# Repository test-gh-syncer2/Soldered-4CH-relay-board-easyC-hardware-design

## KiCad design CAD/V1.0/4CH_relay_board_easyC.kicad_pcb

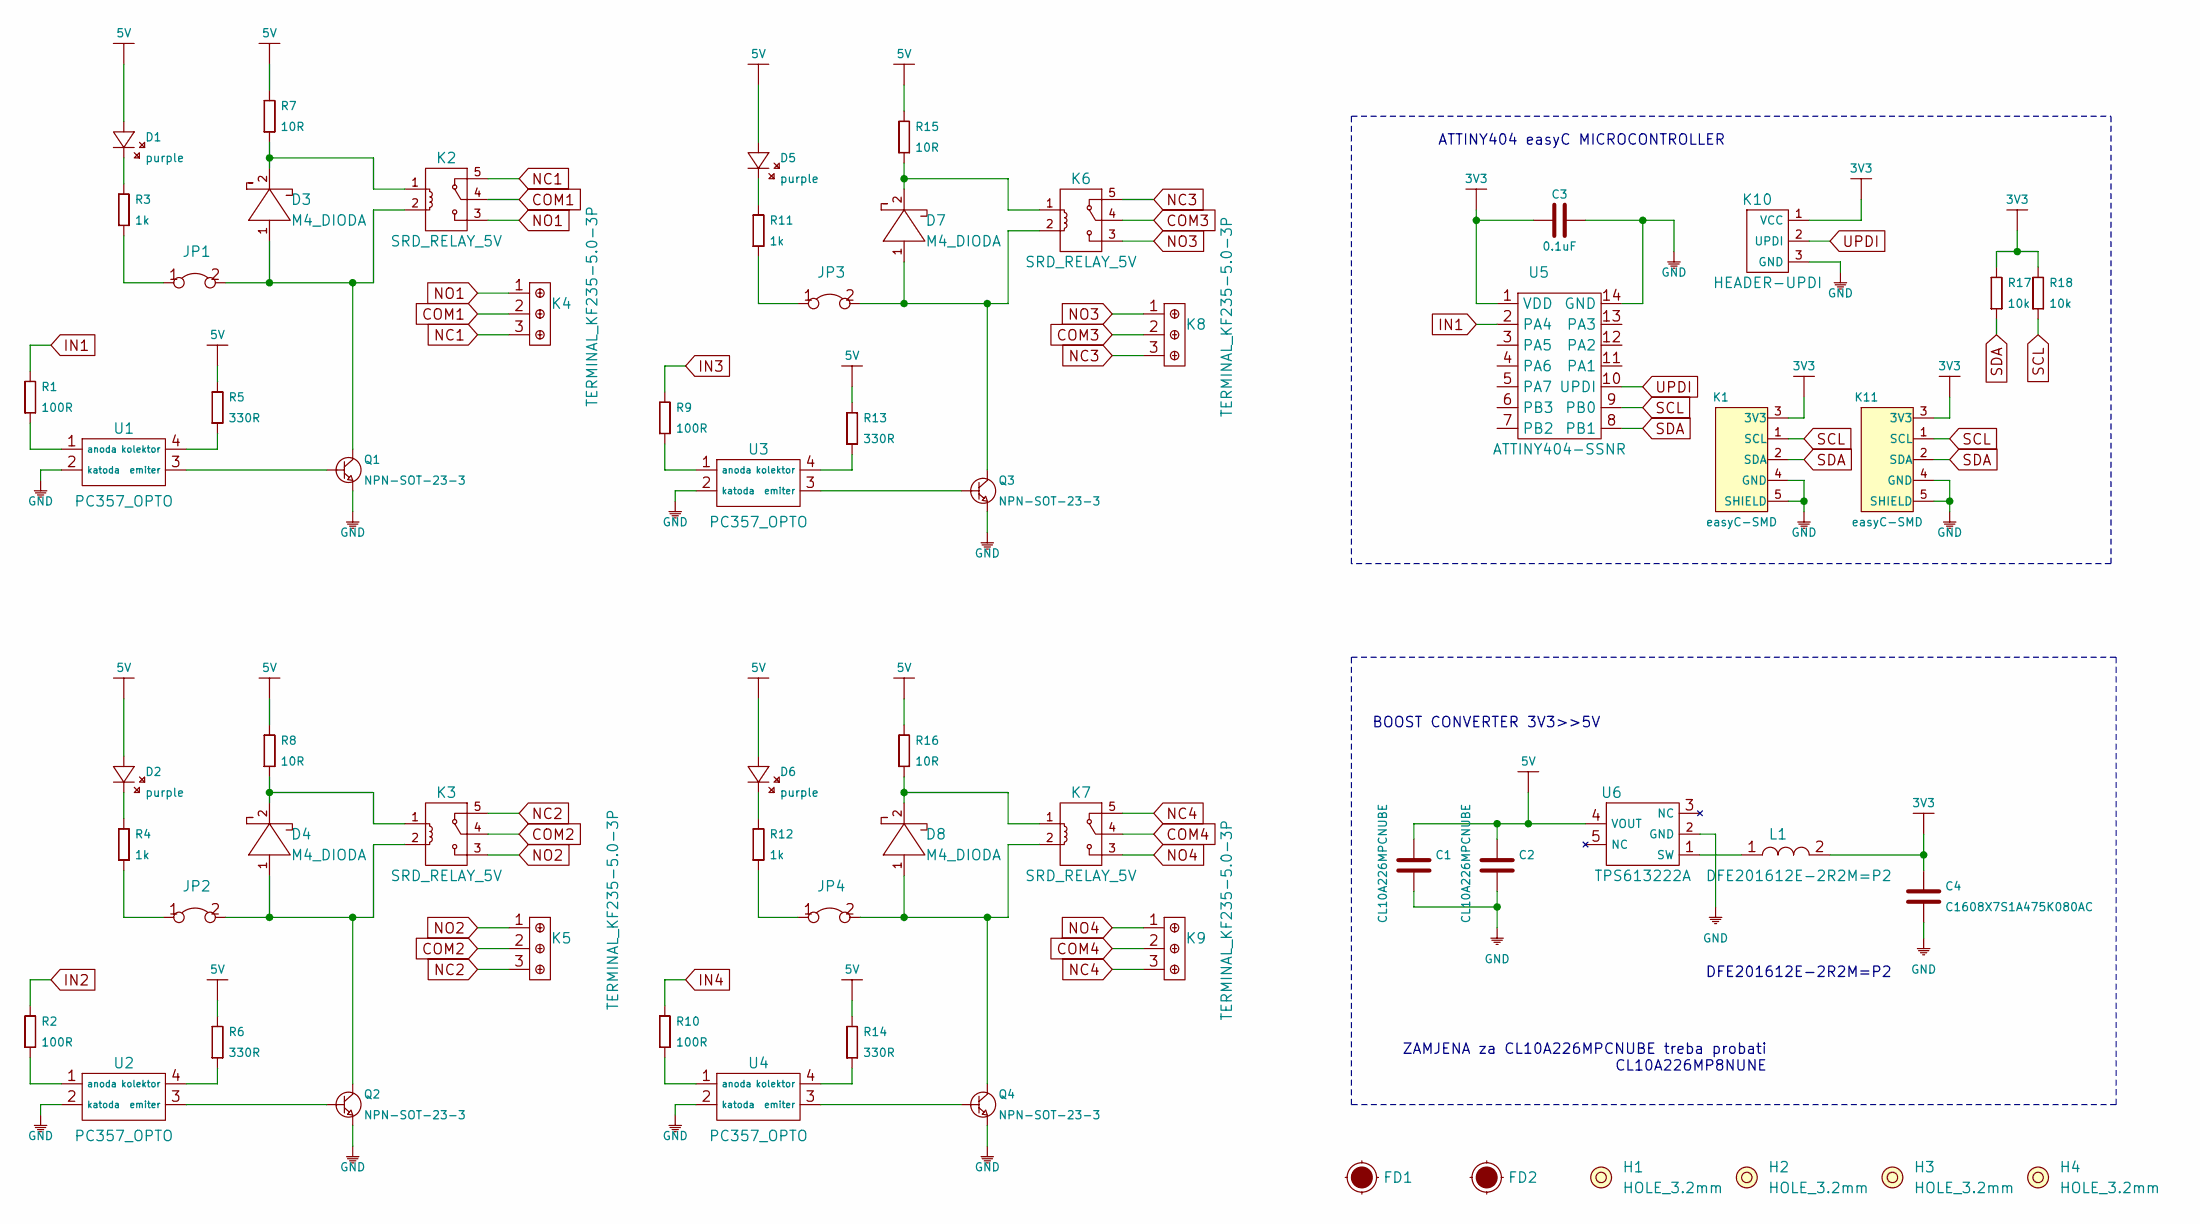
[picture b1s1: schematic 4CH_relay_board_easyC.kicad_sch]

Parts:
C1, C2: CL10A226MPCNUBE; 0603C
C3: 0.1uF; 0603C
C4: C1608X7S1A475K080AC; 0603C
D1, D2, D5, D6: purple; 0402LED
D3, D4, D7, D8: M4_DIODA
FD1, FD2: Fiducial_Stencil; FIDUCIAL_1MM_PASTE
H1, H2, H3, H4: HOLE_3.2mm
JP1, JP2, JP3, JP4: SMD-JUMPER-CONNECTED_TRACE_NOSLODERMASK
K1, K11: easyC-SMD; easyC-connector
K2, K3, K6, K7: SRD_RELAY_5V
K4, K5, K8, K9: TERMINAL_KF235-5.0-3P
K10: HEADER-UPDI
L1: DFE201612E-2R2M=P2; 0806L
Q1, Q2, Q3, Q4: NPN-SOT-23-3; SOT-23-3
R1, R2, R9, R10: 100R; 0603R
R3, R4, R11, R12: 1k; 0402R
R5, R6, R13, R14: 330R; 0603R
R7, R8, R15, R16: 10R; 0603R
R17, R18: 10k; 0603R
U1, U2, U3, U4: PC357_OPTO
U5: ATTINY404-SSNR; SOIC-14
U6: TPS613222A; tps613222a

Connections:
3V3: C3.1, C4.2, K1.3 (3V3), K10.1 (VCC), K11.3 (3V3), L1.2, R17.2, R18.2, U5.1 (VDD)
5V: C1.2, C2.2, D1.1 (A), D2.1 (A), D5.1 (A), D6.1 (A), R5.2, R6.2, R7.2, R8.2, R13.2, R14.2, R15.2, R16.2, U6.4 (VOUT)
COM1: K2.4, K4.2
COM2: K3.4, K5.2
COM3: K6.4, K8.2
COM4: K7.4, K9.2
GND: C1.1, C2.1, C3.2, C4.1, K1.4 (GND), K1.5 (SHIELD), K10.3 (GND), K11.4 (GND), K11.5 (SHIELD), Q1.2 (E), Q2.2 (E), Q3.2 (E), Q4.2 (E), U1.2 (katoda), U2.2 (katoda), U3.2 (katoda), U4.2 (katoda), U5.14 (GND), U6.2 (GND)
IN1: R1.2, U5.2 (PA4)
IN2: R2.2
IN3: R9.2
IN4: R10.2
NC1: K2.5, K4.3
NC2: K3.5, K5.3
NC3: K6.5, K8.3
NC4: K7.5, K9.3
NO1: K2.3, K4.1
NO2: K3.3, K5.1
NO3: K6.3, K8.1
NO4: K7.3, K9.1
unnamed: D1.2 (K), R3.2
unnamed: D2.2 (K), R4.2
unnamed: D3.1 (A), JP1.2, K2.2, Q1.3 (C)
unnamed: D3.2 (K), K2.1, R7.1
unnamed: D4.1 (A), JP2.2, K3.2, Q2.3 (C)
unnamed: D4.2 (K), K3.1, R8.1
unnamed: D5.2 (K), R11.2
unnamed: D6.2 (K), R12.2
unnamed: D7.1 (A), JP3.2, K6.2, Q3.3 (C)
unnamed: D7.2 (K), K6.1, R15.1
unnamed: D8.1 (A), JP4.2, K7.2, Q4.3 (C)
unnamed: D8.2 (K), K7.1, R16.1
unnamed: JP1.1, R3.1
unnamed: JP2.1, R4.1
unnamed: JP3.1, R11.1
unnamed: JP4.1, R12.1
unnamed: L1.1, U6.1 (SW)
unnamed: Q1.1 (B), U1.3 (emiter)
unnamed: Q2.1 (B), U2.3 (emiter)
unnamed: Q3.1 (B), U3.3 (emiter)
unnamed: Q4.1 (B), U4.3 (emiter)
unnamed: R1.1, U1.1 (anoda)
unnamed: R2.1, U2.1 (anoda)
unnamed: R5.1, U1.4 (kolektor)
unnamed: R6.1, U2.4 (kolektor)
unnamed: R9.1, U3.1 (anoda)
unnamed: R10.1, U4.1 (anoda)
unnamed: R13.1, U3.4 (kolektor)
unnamed: R14.1, U4.4 (kolektor)
SCL: K1.1 (SCL), K11.1 (SCL), R18.1, U5.9 (PB0)
SDA: K1.2 (SDA), K11.2 (SDA), R17.1, U5.8 (PB1)
UPDI: K10.2 (UPDI), U5.10 (UPDI)

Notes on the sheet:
BOOST CONVERTER 3V3>>5V
ATTINY404 easyC MICROCONTROLLER
ZAMJENA za CL10A226MPCNUBE treba probati CL10A226MP8NUNE
DFE201612E-2R2M=P2

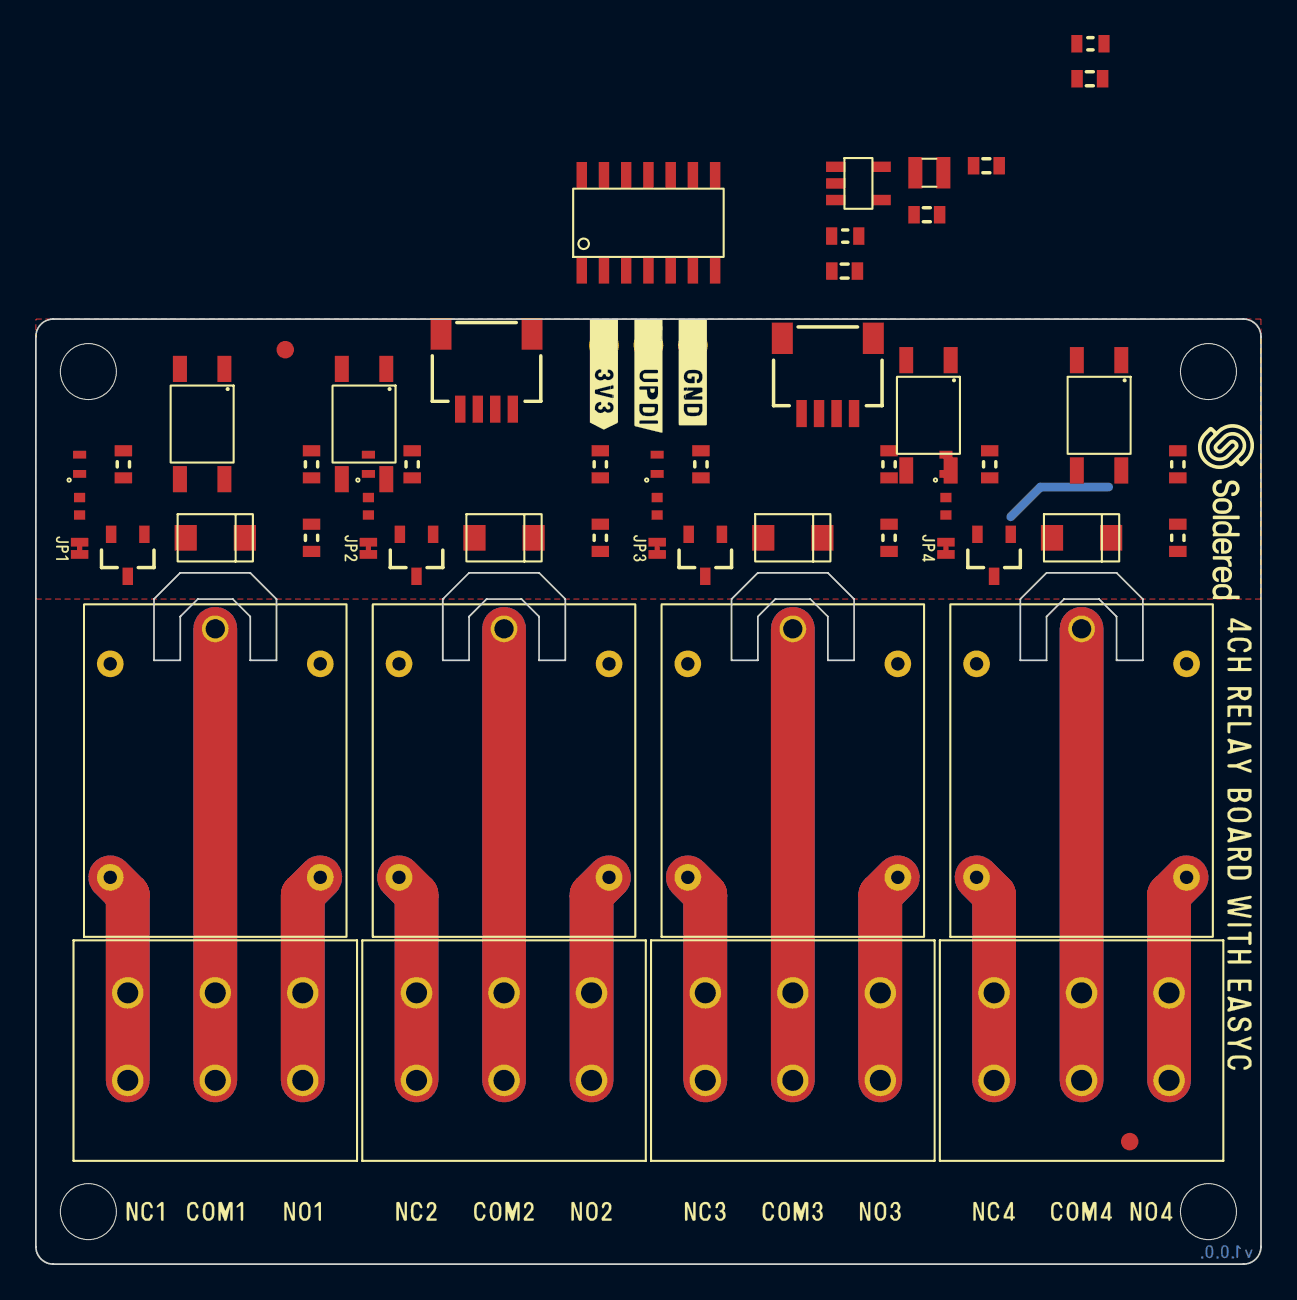
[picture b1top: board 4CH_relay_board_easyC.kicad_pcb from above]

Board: 2 copper layers, 70.0 x 54.0 mm, 62 parts (0 on the bottom side), 48 nets.

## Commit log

2021-09-23 Syncing to git
2021-09-23 Updating open source files.
